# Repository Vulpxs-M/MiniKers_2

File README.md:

# MiniKers_2

Self powered automatics with brushless motor and energy regeneration (as well as some smart IoT capability)

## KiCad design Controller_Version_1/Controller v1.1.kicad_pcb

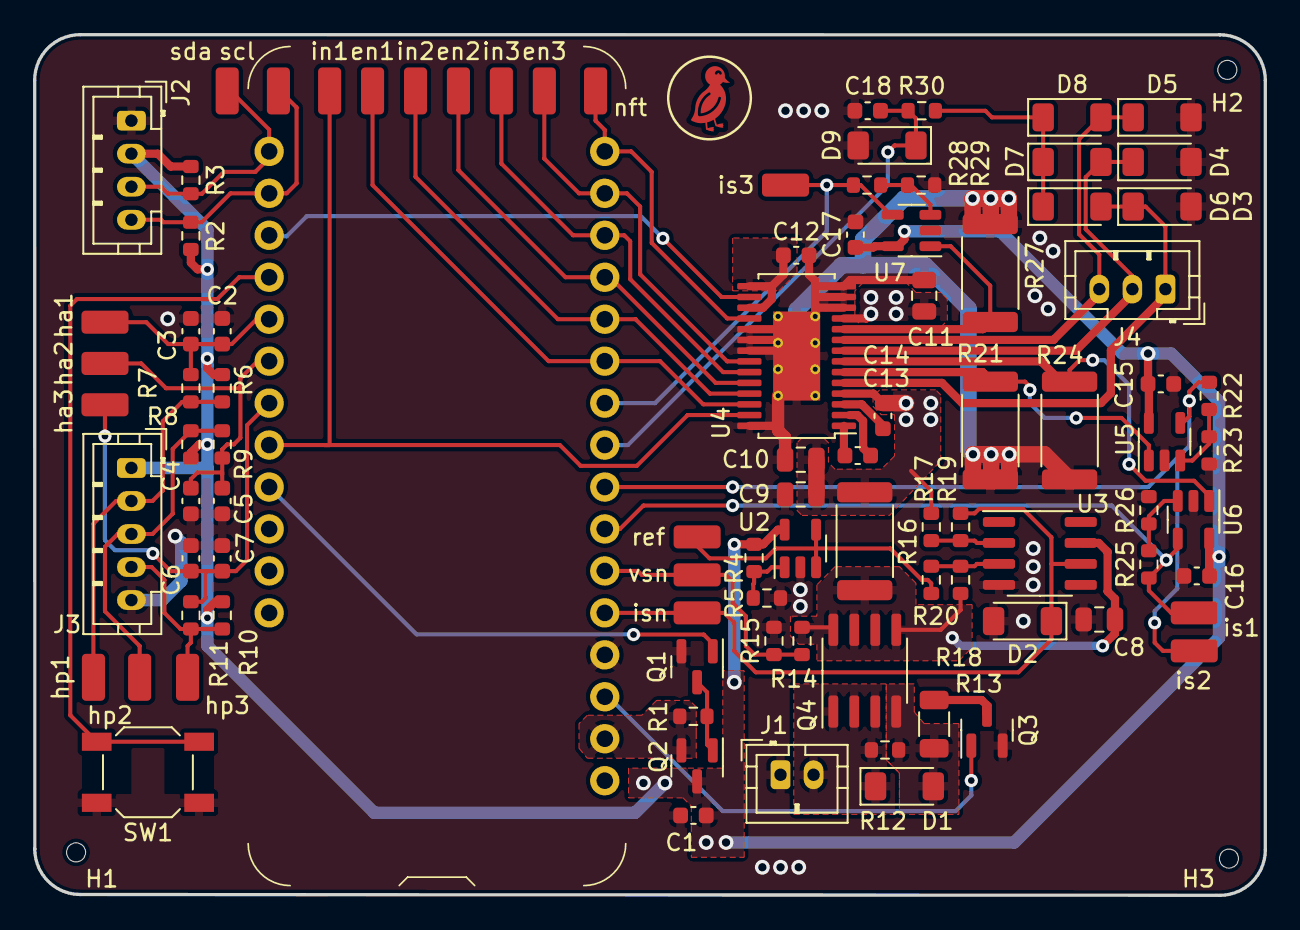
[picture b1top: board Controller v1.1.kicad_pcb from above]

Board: 2 copper layers, 74.5 x 52.1 mm, 98 parts (0 on the bottom side), 52 nets.

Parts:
C1, C14, C15, C16, C17, C18: CC0603KRX7R9BB104 (YAGEO) - 50V 100nF X7R ±10% 06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; C_0603_1608Metric
C2, C3, C4, C5, C6, C7: 0603B153K500NT (FH(Guangdong Fenghua Advanced Tec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; C_0603_1608Metric
C8, C10, C11: CL21B104KCFNNNE (Samsung Electro-Mechanics) - 100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; C_0805_2012Metric
C9: GRM21BR61H106KE43L (Murata Electronics) - 50V 10u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; C_0805_2012Metric
C12: CL10B474KA8NNNC (Samsung Electro-Mechanics) - 25V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; C_0603_1608Metric
C13: 0603B103K500NT (FH(Guangdong Fenghua Advanced Tec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; C_0603_1608Metric
D1: ZMM5245B_R1_10001 (PANJIT International) - 100nA@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; D_MiniMELF
D2: ZMM3V0-M (ST(Semtech)) - 4μA@1V 85Ω Single 2.8V~3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; D_MiniMELF
D3, D4, D5, D6, D7, D8: LL4148 (ST(Semtech)) - 75V +175℃@(Tj) 500mW 1V@10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; D_MiniMELF
D9: TCLLZ3V6TR (Tak Cheong) - 10μA@1V ±5% 100Ω Single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; D_MiniMELF
H1, H2, H3: JlcToolingHole_1.152mm
J1: B2B-PH-K (JST); JST_PH_B2B-PH-K_1x02_P2.00mm_Vertical
J2: B4B-PH-K (JST); JST_PH_B4B-PH-K_1x04_P2.00mm_Vertical
J3: B5B-PH-K (JST); JST_PH_B5B-PH-K_1x05_P2.00mm_Vertical
J4: B3B-PH-K (JST); JST_PH_B3B-PH-K_1x03_P2.00mm_Vertical
Q1, Q3: 2N7002 (Changjiang Electronics Tech (CJ)) - 60V 1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; SOT-23
Q2: SI2301CDS-T1-GE3 (Vishay Intertech) - 20V 3.1A 86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; SOT-23
Q4: DMG4407SSS-13 (Diodes Incorporated) - 30V 9.9A 1.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; SOIC-8_3.9x4.9mm_P1.27mm
R1, R12, R15, R17, R18: 0603WAF1002T5E (UNI-ROYAL(Uniroyal Elec)) - ±1% 1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; R_0603_1608Metric
R2, R3, R6, R7, R8, R9, R10, R11: 0603WAF4701T5E (UNI-ROYAL(Uniroyal Elec)) - ±1% 1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; R_0603_1608Metric
R4: 0603WAF1203T5E (UNI-ROYAL(Uniroyal Elec)) - ±1% 1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; R_0603_1608Metric
R5, R19, R20: 0603WAF1003T5E (UNI-ROYAL(Uniroyal Elec)) - ±1% 1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; R_0603_1608Metric
R13: 1206W4F1001T5 (UNI-ROYAL(Uniroyal Elec)) - ±1% 1/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; R_1206_3216Metric
R14: 0603WAF6802T5E (UNI-ROYAL(Uniroyal Elec)) - ±1% 1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; R_0603_1608Metric
R16: RTT25R050FTE (RALEC) - ±1% 1W Thick Film Resistor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; R_2512_6332Metric
R21, R24, R27: 25121WJ050LT4E (UNI-ROYAL(Uniroyal Elec)) - ±5% 1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; R_2512_6332Metric
R22, R25, R28: 0603WAF3903T5E (UNI-ROYAL(Uniroyal Elec)) - ±1% 1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; R_0603_1608Metric
R23, R26, R29: 0603WAF2002T5E (UNI-ROYAL(Uniroyal Elec)) - ±1% 1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; R_0603_1608Metric
R30: 0603WAF2003T5E (UNI-ROYAL(Uniroyal Elec)) - ±1% 1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; R_0603_1608Metric
SW1: 5.1mm switch; SW_SPST_SKQG_WithoutStem
TP1: 5015 (Keystone) - _mcu_i2c_i2c_link.scl; TestPoint_TE_RCT_0805
TP2: 5015 (Keystone) - i2c_tp._io_sda_link; TestPoint_TE_RCT_0805
TP3: 5015 (Keystone) - _ref_buf_output_link; TestPoint_TE_RCT_0805
TP4: 5015 (Keystone) - _hall_phases_1_link; TestPoint_TE_RCT_0805
TP5: 5015 (Keystone) - _hall_rc[1]_output_link; TestPoint_TE_RCT_0805
TP6: 5015 (Keystone) - _hall_phases_2_link; TestPoint_TE_RCT_0805
TP7: 5015 (Keystone) - _hall_rc[2]_output_link; TestPoint_TE_RCT_0805
TP8: 5015 (Keystone) - _hall_phases_3_link; TestPoint_TE_RCT_0805
TP9: 5015 (Keystone) - _hall_rc[3]_output_link; TestPoint_TE_RCT_0805
TP10: 5015 (Keystone) - _vsense_output_link; TestPoint_TE_RCT_0805
TP11: 5015 (Keystone) - _isense_out_link; TestPoint_TE_RCT_0805
TP12: 5015 (Keystone) - _mcu_gpio_bldc_fault_link; TestPoint_TE_RCT_0805
TP13: 5015 (Keystone) - _mcu_gpio_bldc_en_link.1; TestPoint_TE_RCT_0805
TP14: 5015 (Keystone) - _mcu_gpio_bldc_en_link.2; TestPoint_TE_RCT_0805
TP15: 5015 (Keystone) - _mcu_gpio_bldc_en_link.3; TestPoint_TE_RCT_0805
TP16: 5015 (Keystone) - _mcu_gpio_bldc_in_link.1; TestPoint_TE_RCT_0805
TP17: 5015 (Keystone) - _mcu_gpio_bldc_in_link.2; TestPoint_TE_RCT_0805
TP18: 5015 (Keystone) - _mcu_gpio_bldc_in_link.3; TestPoint_TE_RCT_0805
TP19: 5015 (Keystone) - _curr_amp[1]_output_link; TestPoint_TE_RCT_0805
TP20: 5015 (Keystone) - _curr_amp[2]_output_link; TestPoint_TE_RCT_0805
TP21: 5015 (Keystone) - _curr_amp[3]_output_link; TestPoint_TE_RCT_0805
U1: Feather nRF52840 Express (Adafruit); FEATHERWING_NODIM
U2, U5, U6, U7: LMV321 (Texas Instruments); SOT-23-5
U3: OPA197IDR (Texas Instruments); SOIC-8_3.9x4.9mm_P1.27mm
U4: DRV8313PWP (Texas Instruments); HTSSOP-28-1EP_4.4x9.7mm_P0.65mm_EP2.85x5.4mm_ThermalVias
svg2mod: G***; Symbol_DucklingSolid

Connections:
bldc_drv.cp_cap.neg: C13.2, U4.1
bldc_drv.cp_cap.pos: C13.1, U4.2
bldc_drv.ic.v3p3: C12.1, U4.15, U4.17
bldc_drv.nfault: TP12.1, U1.16, U4.18
bldc_drv.nreset: U1.19, U4.16
bldc_drv.vcp_cap.pos: C14.1, U4.3
curr[1].pwr_out: R21.2, U4.6, U5.1
curr[2].pwr_out: R24.2, U4.7, U6.1
curr[3].pwr_out: R27.2, U4.10, U7.1
curr_amp[1].output: R22.1, TP19.1, U1.8, U5.4
curr_amp[1].r2.a: R22.2, R23.1, U5.3
curr_amp[2].output: R25.1, TP20.1, U1.7, U6.4
curr_amp[2].r2.a: R25.2, R26.1, U6.3
curr_amp[3].output: R28.1, TP21.1, U1.10, U7.4
curr_amp[3].r2.a: R28.2, R29.1, U7.3
gnd: C1.2, C2.2, C3.2, C4.2, C5.2, C6.2, C7.2, C8.2, C9.2, C10.2, C11.2, C12.2, C15.2, C16.2, C17.2, C18.2, D2.2, D3.2, D4.2, D5.2, D9.2, J1.1, J2.1, J3.5, Q1.2, Q3.2, R5.2, R15.2, R21.1, R23.2, R24.1, R26.2, R27.1, R29.2, SW1.2, U1.4, U2.2, U3.4, U4.12, U4.13, U4.14, U4.19, U4.20, U4.21, U4.28, U4.29, U5.2, U6.2, U7.2
hall_pull[1].io: J3.2, R6.2, R7.1, TP4.1
hall_pull[2].io: J3.3, R8.2, R9.1, TP6.1
hall_pull[3].io: J3.4, R10.2, R11.1, TP8.1
hall_rc[1].output: C2.1, C3.1, R7.2, TP5.1, U1.21
hall_rc[2].output: C4.1, C5.1, R9.2, TP7.1, U1.22
hall_rc[3].output: C6.1, C7.1, R11.2, TP9.1, U1.23
hv_gate.control: Q3.1, U1.3
hv_gate.output: C8.1, Q4.5, Q4.6, Q4.7, Q4.8, R14.1, R16.1, R18.1, U3.7
hv_gate.pre.drain: Q3.3, R13.2
hv_gate.pull.b: D1.2, Q4.4, R12.2, R13.1
i2c_pull.i2c.scl: J2.4, R2.2, TP1.1, U1.18
i2c_pull.i2c.sda: J2.3, R3.2, TP2.1, U1.17
isense.amp.r1.b: R17.2, R19.2, U3.2
isense.amp.r2.b: R18.2, R20.2, U3.3
isense.out: D2.1, R19.1, TP11.1, U1.5, U3.6
isense.pwr_out: C9.1, C10.1, C11.1, C14.2, R16.2, R17.1, U4.4, U4.11
lv_gate.control: Q1.1, U1.25
lv_gate.output: C1.1, C15.1, C16.1, C17.1, J2.2, J3.1, Q2.3, R2.1, R3.1, R4.1, R6.1, R8.1, R10.1, U2.5, U5.5, U6.5, U7.5
lv_gate.pre.drain: Q1.3, Q2.1, R1.2
mcu.gpio.bldc_en_1: TP13.1, U1.11, U4.26
mcu.gpio.bldc_en_2: TP14.1, U1.13, U4.24
mcu.gpio.bldc_en_3: TP15.1, U1.15, U4.22
mcu.gpio.bldc_in_1: TP16.1, U1.24, U4.27
mcu.gpio.bldc_in_2: TP17.1, U1.12, U4.25
mcu.gpio.bldc_in_3: TP18.1, U1.14, U4.23
mcu.pwr_out: Q2.2, R1.1, U1.2
motor_pwr.pwr: D1.1, J1.2, Q4.1, Q4.2, Q4.3, R12.1
ref_buf.output: R20.1, TP3.1, U2.3, U2.4
ref_div.output: R4.2, R5.1, U2.1
sw1.out: SW1.1, U1.20
trigger.D4.cathode: D6.1, D7.1, D8.1, R30.1
trigger.bldc_phase_1: D3.1, D6.2, J4.1, U4.5
trigger.bldc_phase_2: D4.1, D7.2, J4.2, U4.8
trigger.bldc_phase_3: D5.1, D8.2, J4.3, U4.9
trigger.trigger_out: C18.1, D9.1, R30.2, U1.9
vsense.output: R14.2, R15.1, TP10.1, U1.6

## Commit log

2023-10-28 [Code] Upload source code for bldc controller v1. This includes driving, voltageand current sensing, hall sensor sensing, and regenerative braking.
2023-11-21 [PCB] Update completed netlist of v1.1 board and configuration settings
2023-11-22 [PCB] Update Controller PCB Design (still unfinished)
2023-11-23 [PCB] Update preliminary version of board layout, to be improved
    Density
    Clean power traces
    (potentially) Smaller diodes
2023-11-24 Changed pin assignments
2023-11-25 [PCB] Finished layout (need to fix duck)
2023-11-25 Repour for Duck
2023-11-26 [PCB] Version ready for order
2023-12-19 [Code] Organize files and incremental update on drive&regen
2023-12-21 [Code] Change switching frequency to 32KHz for minimal audible noise, test compatibility for ball chain
2024-01-13 Calibrated Current Sense Output
2024-01-17 [Code] Configure sensing and data exporting for door deployment
2024-01-19 Cleanup and upload production files
2024-01-19 [Code] Improve regen with dynamically adjusting boost ratio (and attempt to use onboard led)
2024-01-19 [Code] Implement led color change depending on door state
2024-01-22 [Code] Organize files, now ball_chain and door are separate control schemes
2024-01-23 [Code] Working versions for door and ball chain
2024-01-26 [Code] Finalized version used in videos
